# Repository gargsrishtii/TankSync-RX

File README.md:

# TankSync RX — PCB Design

> 2-layer receiver board for a wireless tank monitoring system, built around the ESP32-DevKitC-VE and RYLR998 LoRa module. Designed in KiCad 10.0.

---

## Overview

TankSync RX is the receiver-side PCB of a LoRa-based wireless monitoring system. It receives sensor data transmitted over 868/915 MHz LoRa and processes it via an ESP32 for display and relay control.

**Key features:**
- ESP32-DevKitC-VE as the main controller (Wi-Fi + Bluetooth + dual-core)
- RYLR998 LoRa UART module for long-range wireless communication
- 1.3" OLED display connector (4-pin, I2C)
- WS2812B LED data line with 470Ω series resistor
- 3x status LEDs with 330Ω current-limiting resistors
- JST PH 2.0mm power input connector
- JST XH 3-pin connector for external sensor/data interface
- Berg headers (13-pin + 10-pin) for future relay expansion
- Decoupling capacitors on all power rails
- GND copper pour on both layers

---

## Board Specifications

| Parameter | Value |
|---|---|
| Board size | 80 × 50 mm |
| Layers | 2 (F.Cu + B.Cu) |
| PCB thickness | 1.6 mm |
| Design tool | KiCad 10.0 |
| ERC status | 0 errors, 0 warnings |
| DRC status | 0 errors, 0 unconnected |
| Gerbers | Exported and verified |

---

## Schematic

> *See `/schematic/TankSync_RX_Schematic.pdf` for the full schematic.*

Key design decisions:
- **LORA_RST** tied to ESP32 IO12 with a 10KΩ pull-up (R2) to +3V3, allowing software-controlled LoRa reset
- **R3 (470Ω)** series data resistor from IO32 to LED_DATA line (protects ESP32 GPIO from WS2812B inrush)
- **C6, C7, C8 (100nF SMD)** decoupling capacitors placed close to ESP32 power pins
- **C3, C4 (100µF THT)** bulk decoupling on main power rail — these must remain THT (not changed to SMD)
- **J1 (13-pin) and J2 (10-pin)** Berg headers routed to ESP32 for future relay expansion board

---

## Bill of Materials

| Ref | Qty | Value / Part | Package | Description |
|---|---|---|---|---|
| U1 | 1 | RYLR998 | Castellated 5-pin SMD | REYAX 868/915MHz LoRa UART module |
| U2 | 1 | ESP32-DEVKITC-VE | 38-pin THT dual row | Espressif ESP32 dev board |
| C1 | 1 | 10µF | 0805 SMD | Power rail decoupling |
| C2 | 1 | 47µF | 0805 SMD | Power rail decoupling |
| C3, C4 | 2 | 100µF | Radial THT D5.0mm P2.5mm | Bulk decoupling — must stay THT |
| C6, C7, C8 | 3 | 100nF | 0805 SMD | ESP32 pin decoupling |
| R2 | 1 | 10KΩ | 0805 SMD | LORA_RST pull-up |
| R3 | 1 | 470Ω | 0805 SMD | LED data line series resistor |
| R4, R5, R6 | 3 | 330Ω | 0805 SMD | Status LED current limiters |
| J1 | 1 | Berg 13-pin | PinHeader 1x13 2.54mm | Relay expansion header |
| J2 | 1 | Berg 10-pin | PinHeader 1x10 2.54mm | Relay expansion header |
| J3 | 1 | 1.3" OLED | PinHeader 1x04 2.54mm | OLED display connector |
| J4 | 1 | JST PH 2-pin | JST PH S2B 2.0mm | Power input |
| J5 | 1 | JST XH 3-pin | JST XH B3B 2.5mm | External data connector |
| J6 | 1 | LED Panel | PinHeader 1x04 2.54mm | LED panel connector |

---

## Repository Structure

```
tanksync-pcb/
├── README.md
├── LICENSE
├── images/
│   └── 3D view.png
|   ├── TankSync-rx.png
|   ├── pcb-layout.png
├── gerbers/
│   └── TankSync_RX_Gerbers.zip
├── bom/
│   └── Project1.csv
└── kicad/
    ├── Project1.kicad_pro
    ├── Project1.kicad_sch
    ├── Project1.kicad_pcb
    └── Project1.net
```

---

## Gerber Files

The `/gerbers/` folder contains the complete Gerber set ready for fabrication:

| File | Layer |
|---|---|
| Project1-F_Cu.gbr | Front copper |
| Project1-B_Cu.gbr | Back copper |
| Project1-F_Silkscreen.gbr | Front silkscreen |
| Project1-B_Silkscreen.gbr | Back silkscreen |
| Project1-F_Mask.gbr | Front solder mask |
| Project1-B_Mask.gbr | Back solder mask |
| Project1-F_Paste.gbr | Front solder paste |
| Project1-B_Paste.gbr | Back solder paste |
| Project1-Edge_Cuts.gbr | Board outline |
| Project1-job.gbrjob | Gerber job file |

Recommended fab services: JLCPCB, PCBWay, OSH Park (all accept this Gerber format directly).

---

## Custom Library Dependency

This design uses two custom KiCad components from my public library:

- `MyLibrary:RYLR998_Castellated_5P` — REYAX RYLR998 LoRa module
- `MyLibrary:ESP32-DEVKITC-VE` — Espressif ESP32-DevKitC-VE dev board

**To open this project in KiCad**, you need to add the custom library first:
👉 [gargsrishtii/kicad-parts-library](https://github.com/gargsrishtii/kicad-parts-library)

Follow the installation instructions in that repo's README before opening the `.kicad_sch` or `.kicad_pcb` files.

---

## Pre-fab Checklist (Open Items)

- [ ] Zip and verify Gerbers in a Gerber viewer before ordering
- [ ] Confirm J4 JST PH part number against supplier stock
- [ ] Measure enclosure inner diameter against board outline

---

## Design Tool

- **KiCad 10.0** (PCB design)
- **EasyEDA** (cross-reference for component verification)

---

## License

This hardware design is released under **CERN-OHL-P v2** (Permissive Open Hardware License).
Free to use, modify, and manufacture — no share-alike requirement.
See [LICENSE](LICENSE) for full terms.

---

*Part of the TankSync wireless monitoring system project.*
*Custom KiCad library: [gargsrishtii/kicad-parts-library](https://github.com/gargsrishtii/kicad-parts-library)*

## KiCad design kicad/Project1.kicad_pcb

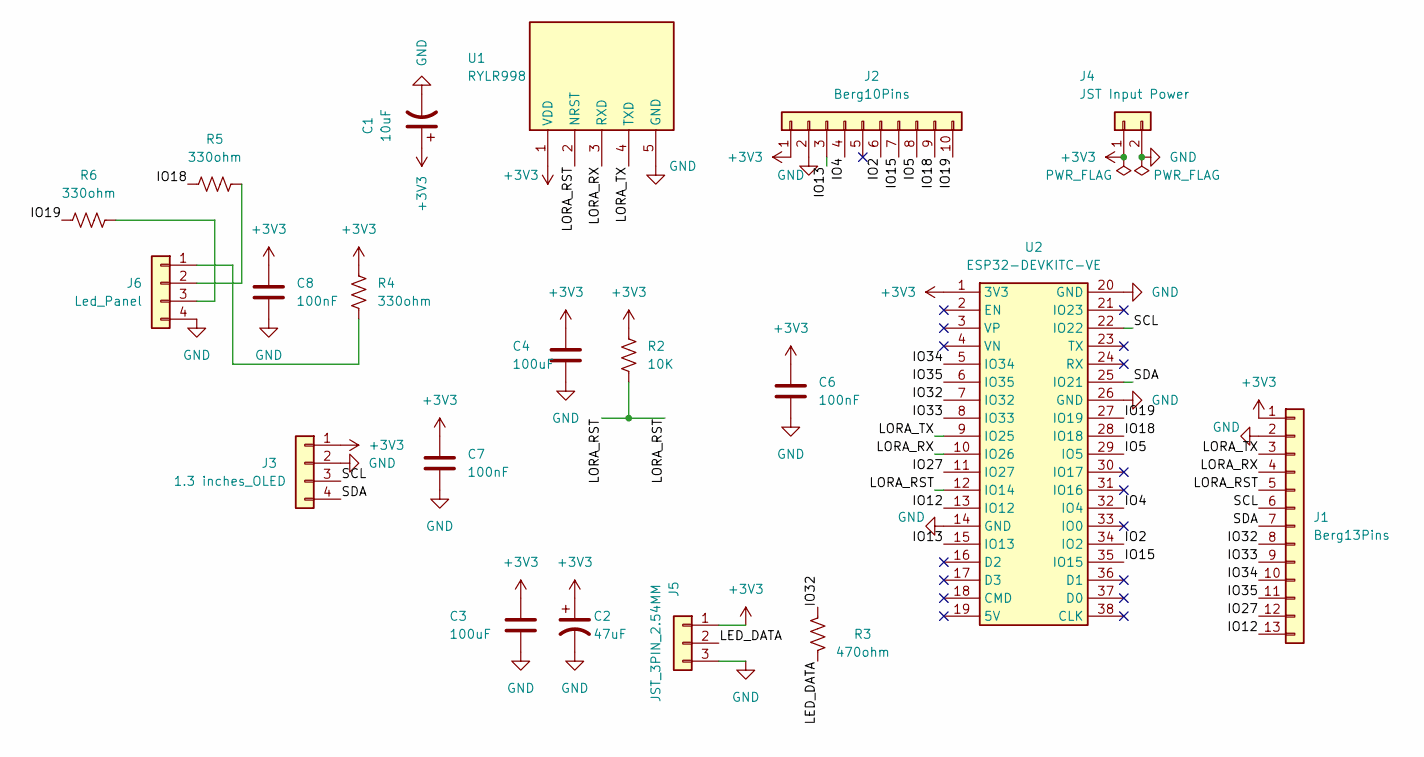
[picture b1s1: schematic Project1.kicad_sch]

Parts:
C1: 10uF; C_0805_2012Metric
C2: 47uF; C_0805_2012Metric
C3, C4: 100uF; CP_Radial_D5.0mm_P2.50mm
C6, C7, C8: 100nF; C_0805_2012Metric
J1: Berg13Pins; PinHeader_1x13_P2.54mm_Vertical
J2: Berg10Pins; PinHeader_1x10_P2.54mm_Vertical
J3: 1.3 inches_OLED; PinHeader_1x04_P2.54mm_Vertical
J4: JST Input Power; JST_PH_S2B-PH-K_1x02_P2.00mm_Horizontal
J5: JST_3PIN_2.54MM; JST_XH_B3B-XH-A_1x03_P2.50mm_Vertical
J6: Led_Panel; PinHeader_1x04_P2.54mm_Vertical
R2: 10K; R_0805_2012Metric
R3: 470ohm; R_0805_2012Metric
R4, R5, R6: 330ohm; R_0805_2012Metric
U1: RYLR998; RYLR998_Castellated_5P
U2: ESP32-DEVKITC-VE

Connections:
+3V3: C1.1, C2.1, C3.1, C4.1, C6.1, C7.1, C8.1, J1.1, J2.1, J3.1, J4.1, J5.1, R2.2, R4.2, U1.1 (VDD), U2.1 (3V3)
/IO2: J2.6, U2.34 (IO2)
/IO4: J2.4, U2.32 (IO4)
/IO5: J2.8, U2.29 (IO5)
/IO12: J1.13, U2.13 (IO12)
/IO13: J2.3, U2.15 (IO13)
/IO15: J2.7, U2.35 (IO15)
/IO18: J2.9, R5.2, U2.28 (IO18)
/IO19: J2.10, R6.2, U2.27 (IO19)
/IO27: J1.12, U2.11 (IO27)
/IO32: J1.8, R3.2, U2.7 (IO32)
/IO33: J1.9, U2.8 (IO33)
/IO34: J1.10, U2.5 (IO34)
/IO35: J1.11, U2.6 (IO35)
/LED_DATA: J5.2, R3.1
/LORA_RST: J1.5, R2.1, U1.2 (NRST), U2.12 (IO14)
/LORA_RX: J1.4, U1.3 (RXD), U2.10 (IO26)
/LORA_TX: J1.3, U1.4 (TXD), U2.9 (IO25)
/SCL: J1.6, J3.3, U2.22 (IO22)
/SDA: J1.7, J3.4, U2.25 (IO21)
GND: C1.2, C2.2, C3.2, C4.2, C6.2, C7.2, C8.2, J1.2, J2.2, J3.2, J4.2, J5.3, J6.4, U1.5 (GND), U2.14 (GND), U2.20 (GND), U2.26 (GND)
unnamed: J6.1, R4.1
unnamed: J6.2, R5.1
unnamed: J6.3, R6.1

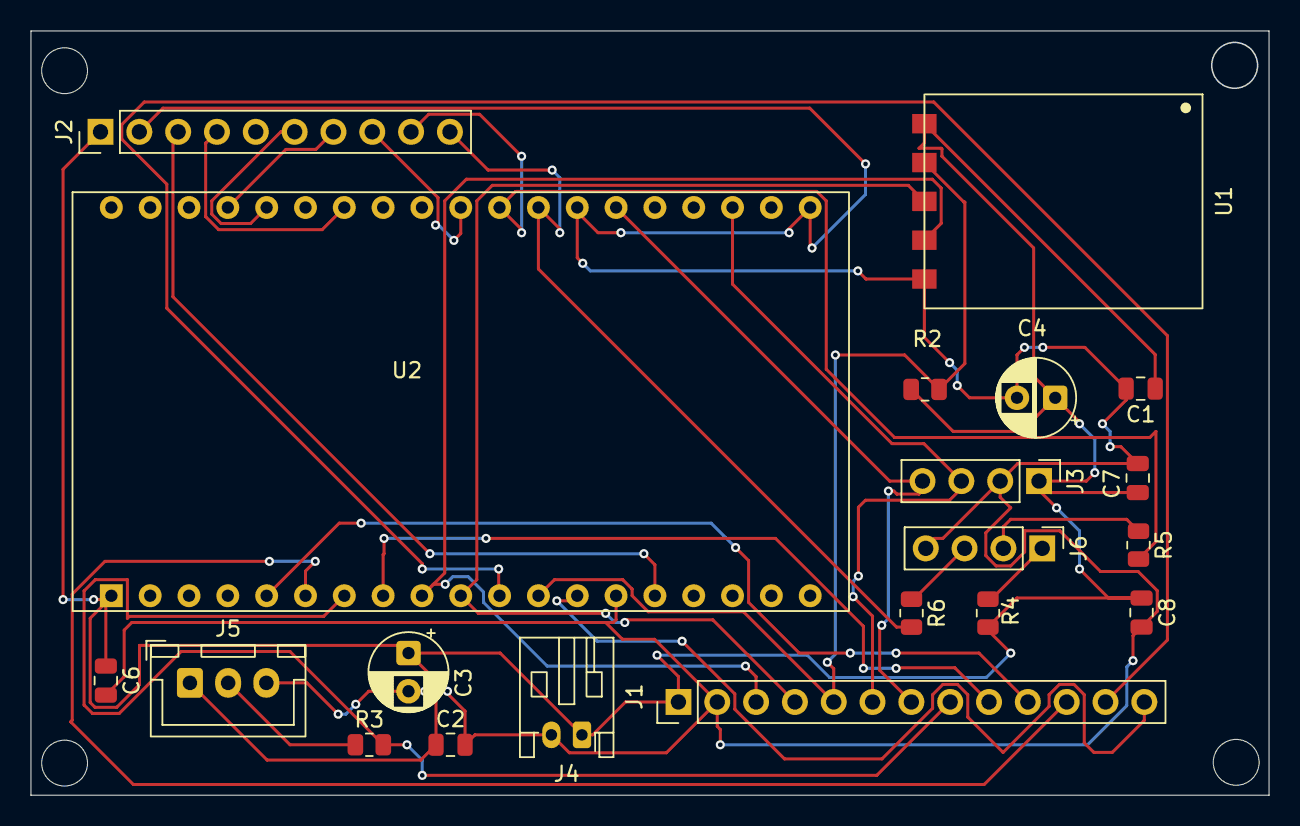
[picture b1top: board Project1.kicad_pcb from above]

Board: 2 copper layers, 81.0 x 50.0 mm, 20 parts (0 on the bottom side), 24 nets.
